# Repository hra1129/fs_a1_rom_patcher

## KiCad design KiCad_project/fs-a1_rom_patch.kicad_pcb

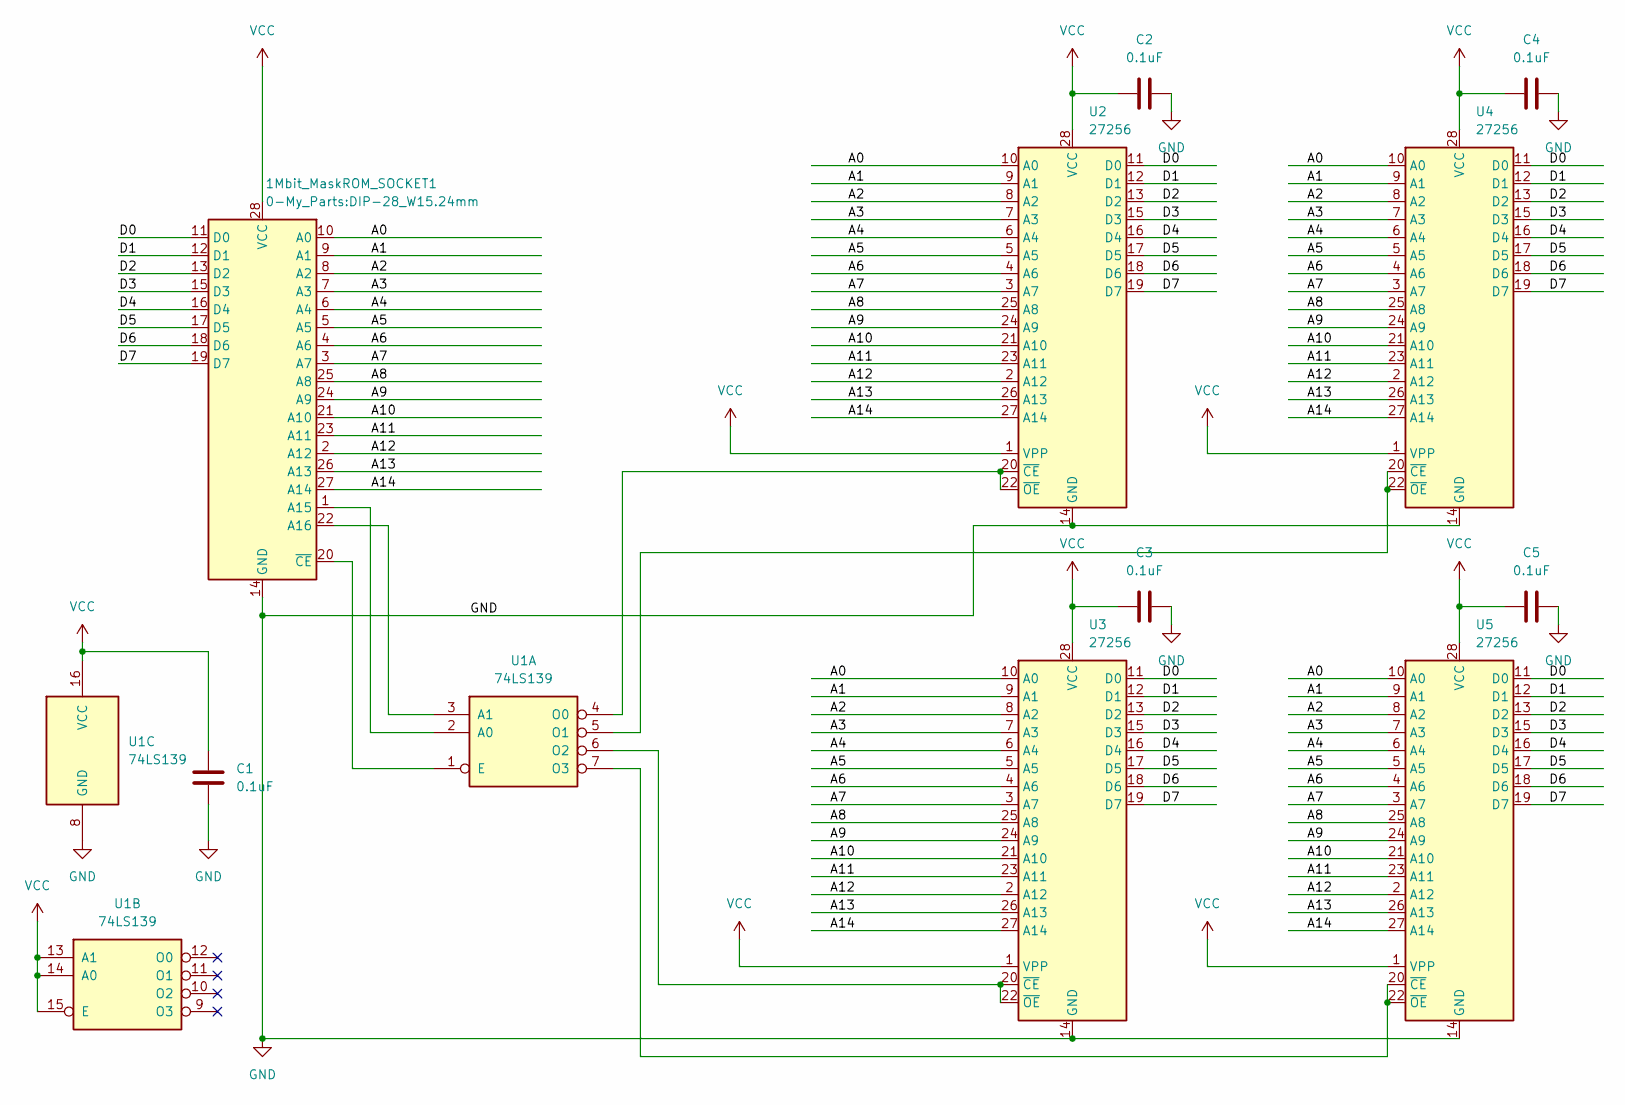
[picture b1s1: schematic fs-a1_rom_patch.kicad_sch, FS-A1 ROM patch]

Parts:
1Mbit_MaskROM_SOCKET1: DIP-28_W15.24mm
C1, C2, C3, C4, C5: 0.1uF; C_0603_1608Metric_Pad1.08x0.95mm_HandSolder
U1: 74LS139; DIP-16_W7.62mm
U2, U3, U4, U5: 27256; DIP-28_W15.24mm

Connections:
/A0: 1Mbit_MaskROM_SOCKET1.10 (A0), U2.10 (A0), U3.10 (A0), U4.10 (A0), U5.10 (A0)
/A1: 1Mbit_MaskROM_SOCKET1.9 (A1), U2.9 (A1), U3.9 (A1), U4.9 (A1), U5.9 (A1)
/A2: 1Mbit_MaskROM_SOCKET1.8 (A2), U2.8 (A2), U3.8 (A2), U4.8 (A2), U5.8 (A2)
/A3: 1Mbit_MaskROM_SOCKET1.7 (A3), U2.7 (A3), U3.7 (A3), U4.7 (A3), U5.7 (A3)
/A4: 1Mbit_MaskROM_SOCKET1.6 (A4), U2.6 (A4), U3.6 (A4), U4.6 (A4), U5.6 (A4)
/A5: 1Mbit_MaskROM_SOCKET1.5 (A5), U2.5 (A5), U3.5 (A5), U4.5 (A5), U5.5 (A5)
/A6: 1Mbit_MaskROM_SOCKET1.4 (A6), U2.4 (A6), U3.4 (A6), U4.4 (A6), U5.4 (A6)
/A7: 1Mbit_MaskROM_SOCKET1.3 (A7), U2.3 (A7), U3.3 (A7), U4.3 (A7), U5.3 (A7)
/A8: 1Mbit_MaskROM_SOCKET1.25 (A8), U2.25 (A8), U3.25 (A8), U4.25 (A8), U5.25 (A8)
/A9: 1Mbit_MaskROM_SOCKET1.24 (A9), U2.24 (A9), U3.24 (A9), U4.24 (A9), U5.24 (A9)
/A10: 1Mbit_MaskROM_SOCKET1.21 (A10), U2.21 (A10), U3.21 (A10), U4.21 (A10), U5.21 (A10)
/A11: 1Mbit_MaskROM_SOCKET1.23 (A11), U2.23 (A11), U3.23 (A11), U4.23 (A11), U5.23 (A11)
/A12: 1Mbit_MaskROM_SOCKET1.2 (A12), U2.2 (A12), U3.2 (A12), U4.2 (A12), U5.2 (A12)
/A13: 1Mbit_MaskROM_SOCKET1.26 (A13), U2.26 (A13), U3.26 (A13), U4.26 (A13), U5.26 (A13)
/A14: 1Mbit_MaskROM_SOCKET1.27 (A14), U2.27 (A14), U3.27 (A14), U4.27 (A14), U5.27 (A14)
/D0: 1Mbit_MaskROM_SOCKET1.11 (D0), U2.11 (D0), U3.11 (D0), U4.11 (D0), U5.11 (D0)
/D1: 1Mbit_MaskROM_SOCKET1.12 (D1), U2.12 (D1), U3.12 (D1), U4.12 (D1), U5.12 (D1)
/D2: 1Mbit_MaskROM_SOCKET1.13 (D2), U2.13 (D2), U3.13 (D2), U4.13 (D2), U5.13 (D2)
/D3: 1Mbit_MaskROM_SOCKET1.15 (D3), U2.15 (D3), U3.15 (D3), U4.15 (D3), U5.15 (D3)
/D4: 1Mbit_MaskROM_SOCKET1.16 (D4), U2.16 (D4), U3.16 (D4), U4.16 (D4), U5.16 (D4)
/D5: 1Mbit_MaskROM_SOCKET1.17 (D5), U2.17 (D5), U3.17 (D5), U4.17 (D5), U5.17 (D5)
/D6: 1Mbit_MaskROM_SOCKET1.18 (D6), U2.18 (D6), U3.18 (D6), U4.18 (D6), U5.18 (D6)
/D7: 1Mbit_MaskROM_SOCKET1.19 (D7), U2.19 (D7), U3.19 (D7), U4.19 (D7), U5.19 (D7)
GND: 1Mbit_MaskROM_SOCKET1.14 (GND), C1.2, C2.1, C3.1, C4.1, C5.1, U1.8 (GND), U2.14 (GND), U3.14 (GND), U4.14 (GND), U5.14 (GND)
unnamed: 1Mbit_MaskROM_SOCKET1.1 (A15), U1.2 (A0)
unnamed: 1Mbit_MaskROM_SOCKET1.22 (A16), U1.3 (A1)
unnamed: 1Mbit_MaskROM_SOCKET1.20 (~CE), U1.1 (E)
unnamed: U1.4 (O0), U2.20 (~CE), U2.22 (~OE)
unnamed: U1.5 (O1), U4.20 (~CE), U4.22 (~OE)
unnamed: U1.6 (O2), U3.20 (~CE), U3.22 (~OE)
unnamed: U1.7 (O3), U5.20 (~CE), U5.22 (~OE)
VCC: 1Mbit_MaskROM_SOCKET1.28 (VCC), C1.1, C2.2, C3.2, C4.2, C5.2, U1.13 (A1), U1.14 (A0), U1.15 (E), U1.16 (VCC), U2.1 (VPP), U2.28 (VCC), U3.1 (VPP), U3.28 (VCC), U4.1 (VPP), U4.28 (VCC), U5.1 (VPP), U5.28 (VCC)

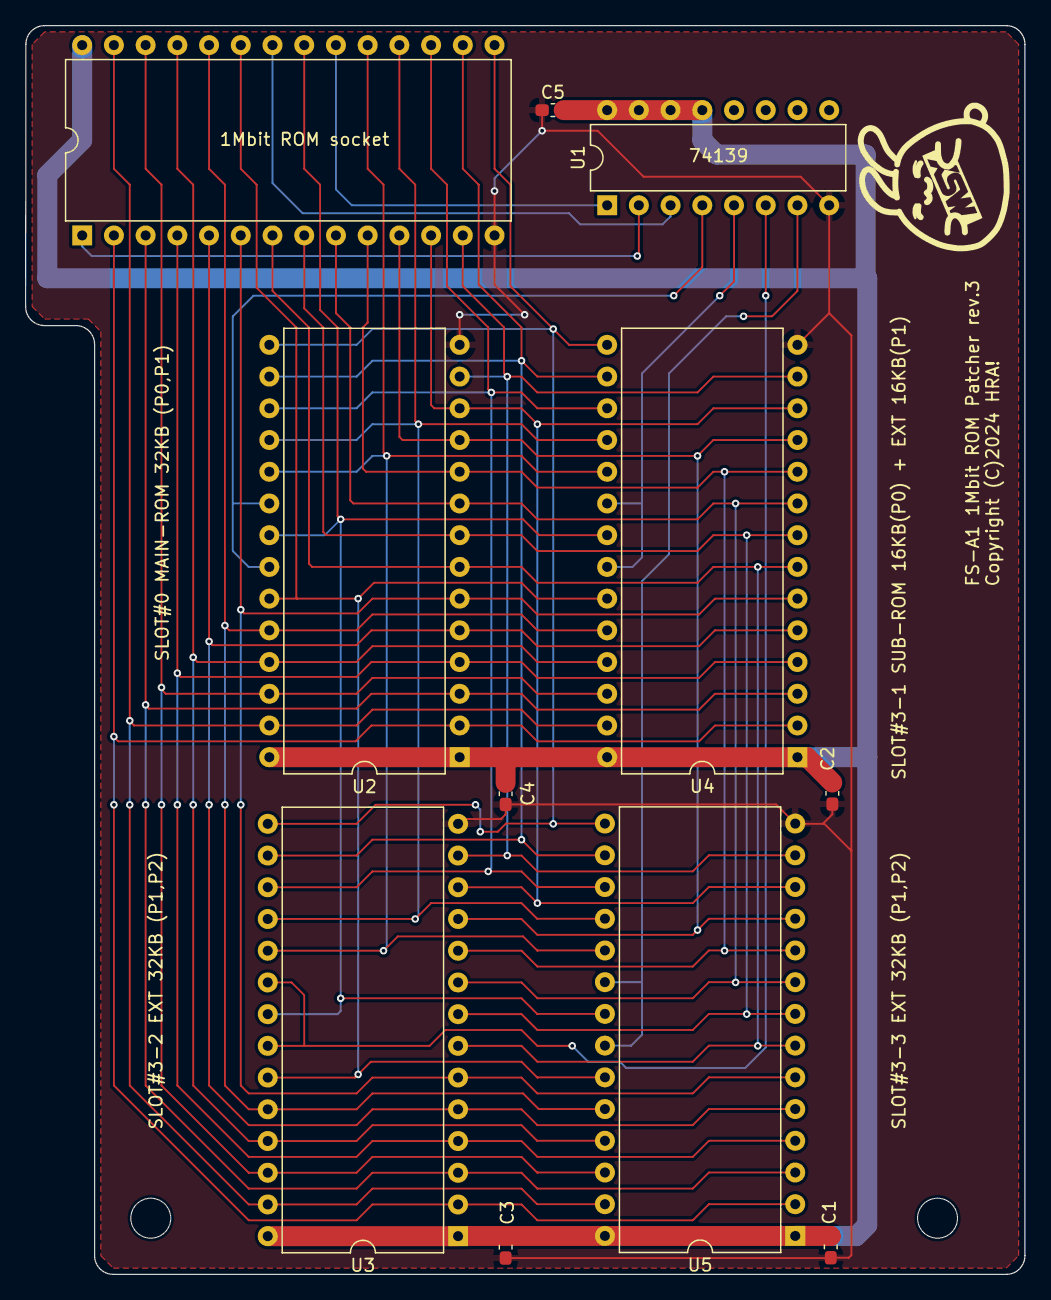
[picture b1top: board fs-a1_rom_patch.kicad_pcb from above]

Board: 2 copper layers, 80.0 x 100.0 mm, 13 parts (0 on the bottom side), 32 nets.

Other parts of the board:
MH3, MH4: MountingHole_3.2mm_M3

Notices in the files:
KiCad_project/fs-a1_rom_patch.kicad_pcb:
Copyright (C)2024 HRA!
